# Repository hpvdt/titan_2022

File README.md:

# TITAN Video System

This is the code and hardware that is used to drive the electronics aboard TITAN for the "drive-by-video" system used for the World Human Powered Speed Challenge 2022.

>[!NOTE]
> This repository is meant to a snapshot of the system used for the 2022 system for TITAN, and was archived in November 2023. It was only unarchived to add a written summary of [operating instructions](./OPERATION.md) should it need to be reused. However no changes to the system itself have happened since 2023.
>
> For information on the the newest system in 2026 please go to that one's [separate repository](https://github.com/savob/titan_2026).

This code is spread across two types of devices, an STM32 microcontroller (STM32F103C8 is used in current models) and Raspberry Pis (RPi) Model 3B+'s. Each rider has an RPi for a total of two units, while there is only one STM32 for the vehicle. The STM32 is primarily responsible for collecting vehicle data and passing it to the RPis when requested. The RPis are responsible for displaying the video feed from the RPi Cameras used (hence why each rider needs their own) with an overlay of data collected inside the vehicle. This overlay is tailored to each rider.

There is an additional redundant video system for the front rider based on analog video to minimize potential failure points. This system was entirely off the shelf except for the power regulator, and was entirely disconnected from the remainder of TITAN's electronics to prevent any failure cascade affecting it.

## Folders

The repository is split into folders based on function.

Folder | Purpose
------ | -------
`Hardware` | Hardware files for our circuit boards
`Microcontroller Code` | STM32 Code
`vision` | RPi video code in C

## Hardware

The hardware for TITAN was all designed in [KiCad](https://www.kicad.org/) there are all three boards designed for TITAN with a `readme.md` explaining their purposes. Below is a block diagram of the TITAN system.

## Microcontroller Code

This is the collection of code prepared for the microcontroller on TITAN. It contains the unit tests we prepared when developing and testing different features that would eventually be integrated into TITAN, a local copy of the GPS library we use, and the overall program for TITAN.

TITAN was initially coded entirely within the Arduino IDE, however we migrated to using VS Code and PlatformIO to help make development easier and also make use of debugging features absent in the original Arduino IDE.

## Raspberry Pi Code

These are responsible for putting video on the displays for the riders to see, overlaid with information about TITAN. One of the RPi's has an ANT+ USB module used to collect data from the heart rate monitor and power pedals each rider has and feed it to the STM32 to pass onto the other RPi.

**The program for running the video feed is run as a separate process to the overlay**, this way if there is a hardware malfunction for the overlay (e.g. the STM32 freezes) then the video feed is uninterrupted for the riders.

The code for vision is split between Python and C. The video related code is written in Python, as well as a few other scripts for operation. The overlay code is written in C using the chipset driver library unique to the RPi 3 hardware to draw the overlay so it cannot be used on RPi models other then the 3B or 3B+ (and must be compiled specifically for each model).

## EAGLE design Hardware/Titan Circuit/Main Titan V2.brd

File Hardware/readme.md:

# TITAN Hardware

These folders contain the files related to hardware designed to operate TITAN. They were all designed using KiCad 6.0.2.

## Overview

The TITAN hardware is designed to primarily be a HAT (**HA**rdware on **T**op) for the Raspberry Pi 3B+s we use for video. This form factor was chosen to reduce the overall footprint of the system compared to the original 2019 system which used a ribbon cable between the RPi and boards. This also reduces the chance of incorrect connections since the HAT can only be seated one way. At the heart of the HAT, there is an STM32F103C microcontroller which communicates with the RPis and various sensors around TITAN via the various connections present.

These HATs perform 4 main functions:
1. Regulate power for their RPi and monitor from the battery. (Reverse polarity and undervoltage protection built in).
2. Facilitate communication between RPis via an STM32 microcontroller
3. Collect data from TITAN using the STM32 microcontroller
4. Handle telemetry with the chase vechicle

**Functions 2 to 4 are only performed on the "main" (front) unit, where the STM32 is.** The secondary (rear) does not have the STM32 mounted and just uses the power system and a header to connect to the main board for data.

## The Boards

There are three boards/folders/projects present in the folder, representing two revisions of the hardware. 

### TITAN Redux (2020)

Following feedback from the 2019 WHPSC and experience in developing [Blueshift](https://github.com/hpvdt/blueshift), an initial revision of TITAN was made in the fall of 2020, dubbed `titan_redux`. This was the main revision from the 2019 system, moving to the HAT form factor which worked on Blueshift as well as moving to embed the microconroller directly on the board (as opposed to seating a "Blue Pill" development board) and using SMT to reduce the overall size.

This was largely successful and allowed most of the code that went into TITAN in 2022 to be properly tested. There were only two notable issues with it:
1. The RX and TX lines for the GPS were not properly crossed over to the STM32.
2. The 5V regulator was removed for undocumented reasons, likely due to a failure.

### TITAN 2022

The more straightforwardly named `titan_2022` is a revision of the Redux board. It addresses the issues it had as well as adding support for new features while maintaining the same RPi HAT form. A brief of the changes:

- Fixed UART lines
- Rearranged board for improved button access
- Rearranged sensors to simplify routing
- Changed to a different 5V regulator (largely due to supply issues)
- Moved DHT sensor and encoder comparator off-board
- Added headers for monitoring CO2 and brake temperature

### TITAN Wheel (2022)

As part of the revision process from redux to the 2022 system a daughter board to collect wheel data was prepared called `titan_wheel`. This board houses the brake temperature sensor as well as the optical encoder and its conditioning circuitry. It was designed to fit within the wheel structure close to the brake disk.

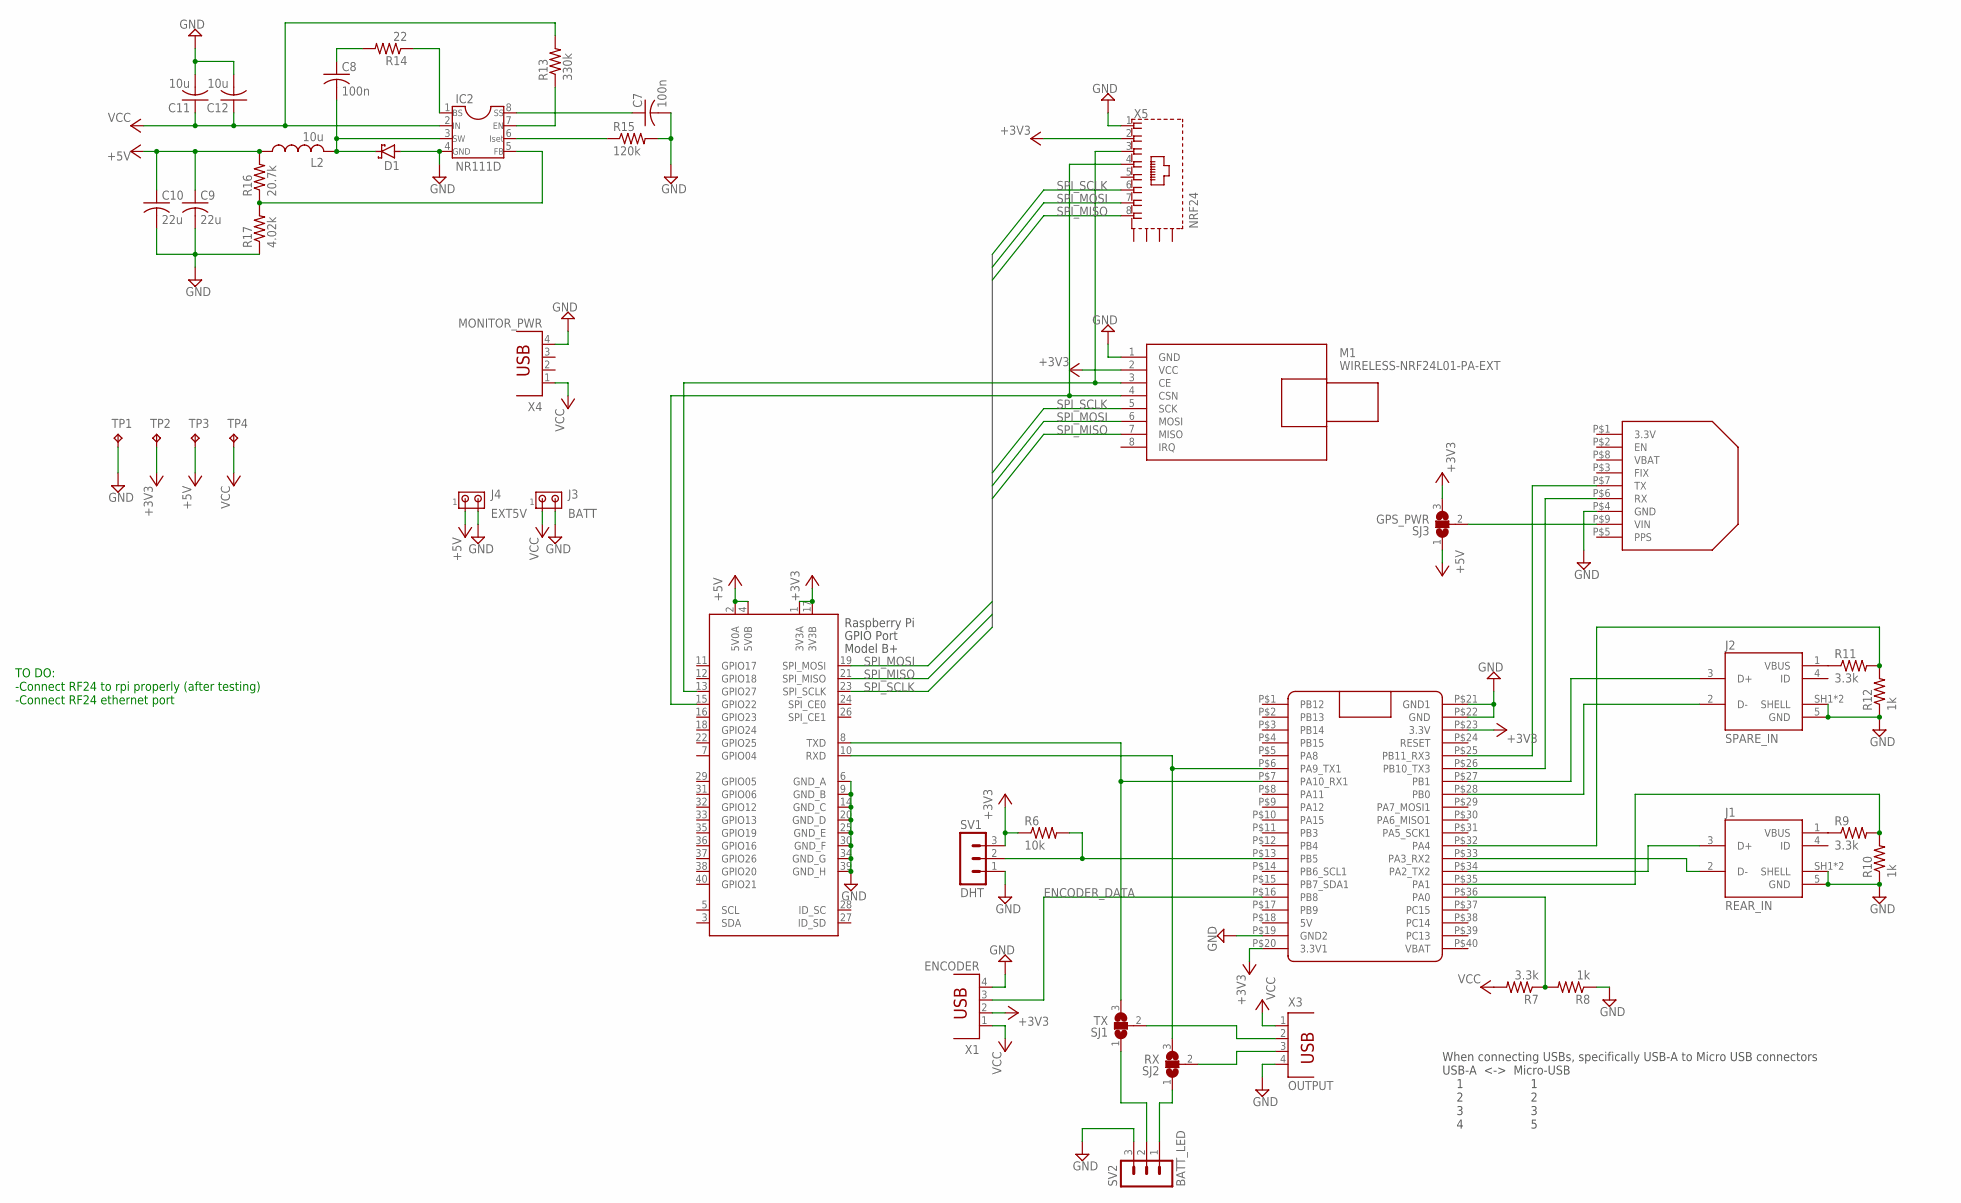
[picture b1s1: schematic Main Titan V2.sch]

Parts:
C7, C8: 100n; C050-024X044
C9, C10: 22u; C025-024X044
C11, C12: 10u; C025-024X044
D1: SCHOTTKY-DIODEC4111-15; C4111-15
IC2: NR111D; DIL08
J1: REAR_IN; TE_2172034-1
J2: SPARE_IN; TE_2172034-1
J3: BATT; 1X2MTA
J4: EXT5V; 1X2MTA
L2: 10u; INDRD650W105D880H1100B
M1: WIRELESS-NRF24L01-PA-EXT
R6: 10k; 0204/7
R7, R9, R11: 3.3k; 0204/7
R8, R10, R12: 1k; 0204/7
R13: 330k; 0204/7
R14: 22; 0204/7
R15: 120k; 0204/7
R16: 20.7k; 0204/7
R17: 4.02k; 0204/7
SJ1: TX; SJ_2
SJ2: RX; SJ_2
SJ3: GPS_PWR; SJ_2
SV1: DHT; MA03-1
SV2: BATT_LED; MA03-1
TP1: GND; TP20SQ
TP2: 3V3; TP20SQ
TP3: 5V; TP20SQ
TP4: BAT; TP20SQ
U$1: BLUE_PILL
U$3: ULTIMATE-GPS; ULTIMATE_GPS
X1: ENCODER; PN87520
X2: RPI; RASPI_GPIO_B+_BOX
X3: OUTPUT; PN87520
X4: MONITOR_PWR; PN87520
X5: NRF24; RJ45-SHIELD1

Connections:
3.3V: U$3.P$1 (3.3V)
25%LED: SJ1.1, SV2.2
50%LED: SJ2.1, SV2.1
+3V3: M1.2 (VCC), R6.1, SJ3.3, SV1.3, TP2.TP, U$1.P$20 (3.3V1), U$1.P$23 (3.3V), X1.2, X2.1 (3V3A), X2.17 (3V3B), X5.2
+5V: C9.1, C10.1, J4.1, L2.1, R16.2, SJ3.1, TP3.TP, X2.2 (5V0A), X2.4 (5V0B)
BATT_LVL: R7.1, R8.2, U$1.P$36 (PA0)
DHT: R6.2, SV1.2, U$1.P$13 (PB5)
ENCODER_DATA: U$1.P$16 (PB8), X1.3
GND: C7.2, C9.2, C10.2, C11.2, C12.2, D1.A, IC2.4 (GND), J1.5 (GND), J1.SH1 (SHELL), J1.SH2 (SHELL), J2.5 (GND), J2.SH1 (SHELL), J2.SH2 (SHELL), J3.2, J4.2, M1.1 (GND), R8.1, R10.1, R12.1, R15.2, R17.1, SV1.1, SV2.3, TP1.TP, U$1.P$19 (GND2), U$1.P$21 (GND1), U$1.P$22 (GND), U$3.P$4 (GND), X1.4, X2.6 (GND_A), X2.9 (GND_B), X2.14 (GND_C), X2.20 (GND_D), X2.25 (GND_E), X2.30 (GND_F), X2.34 (GND_G), X2.39 (GND_H), X3.4, X4.4, X5.1
GPS_RX: U$1.P$26 (PB10_TX3), U$3.P$6 (RX)
GPS_TX: U$1.P$25 (PB11_RX3), U$3.P$7 (TX)
unnamed: M1.3 (CE), X2.13 (GPIO27), X5.3
unnamed: M1.4 (CSN), X2.15 (GPIO22), X5.4
unnamed: SJ1.2, X3.2
unnamed: SJ3.2, U$3.P$9 (VIN)
unnamed: SJ2.2, X3.3
unnamed: IC2.5 (FB), R16.1, R17.2
unnamed: J1.1 (VBUS), R9.1
unnamed: J2.1 (VBUS), R11.1
unnamed: C8.2, D1.C, IC2.3 (SW), L2.2
unnamed: C8.1, R14.2
unnamed: C7.1, IC2.8 (SS)
unnamed: IC2.6 (ISET), R15.1
unnamed: IC2.7 (EN), R13.1
unnamed: IC2.1 (BS), R14.1
REARBATT: R9.2, R10.2, U$1.P$35 (PA1)
REARRX: J1.3 (D+), U$1.P$34 (PA2_TX2)
REARTX: J1.2 (D-), U$1.P$33 (PA3_RX2)
RPI_RX: SJ2.3, U$1.P$6 (PA9_TX1), X2.10 (RXD)
RPI_TX: SJ1.3, U$1.P$7 (PA10_RX1), X2.8 (TXD)
SPAREBATT: R11.2, R12.2, U$1.P$32 (PA4)
SPARELED1: J2.3 (D+), U$1.P$27 (PB1)
SPARELED2: J2.2 (D-), U$1.P$28 (PB0)
SPI_MISO: M1.7 (MISO), X2.21 (SPI_MISO), X5.8
SPI_MOSI: M1.6 (MOSI), X2.19 (SPI_MOSI), X5.7
SPI_SCLK: M1.5 (SCK), X2.23 (SPI_SCLK), X5.6
VCC: C11.1, C12.1, IC2.2 (IN), J3.1, R7.2, R13.2, TP4.TP, X1.1, X3.1, X4.1

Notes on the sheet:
When connecting USBs, specifically USB-A to Micro USB connectors USB-A <-> Micro-USB 1 1 2 2 3 3 4 5
TO DO: -Connect RF24 to rpi properly (after testing) -Connect RF24 ethernet port

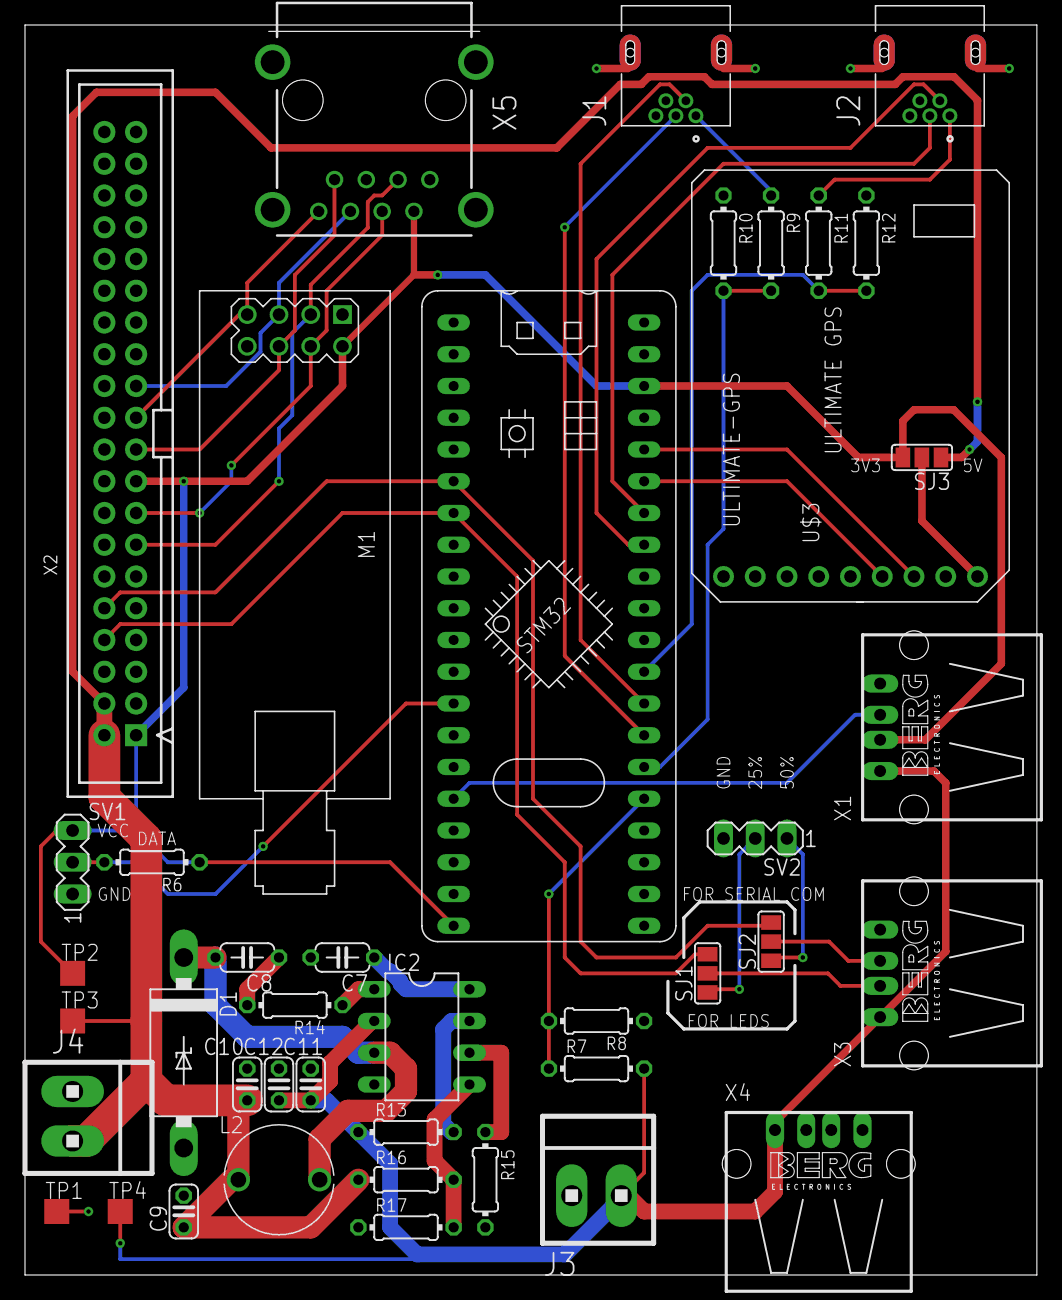
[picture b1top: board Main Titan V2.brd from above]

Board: 2 copper layers, 80.9 x 100.0 mm, 42 parts (0 on the bottom side), 36 nets.

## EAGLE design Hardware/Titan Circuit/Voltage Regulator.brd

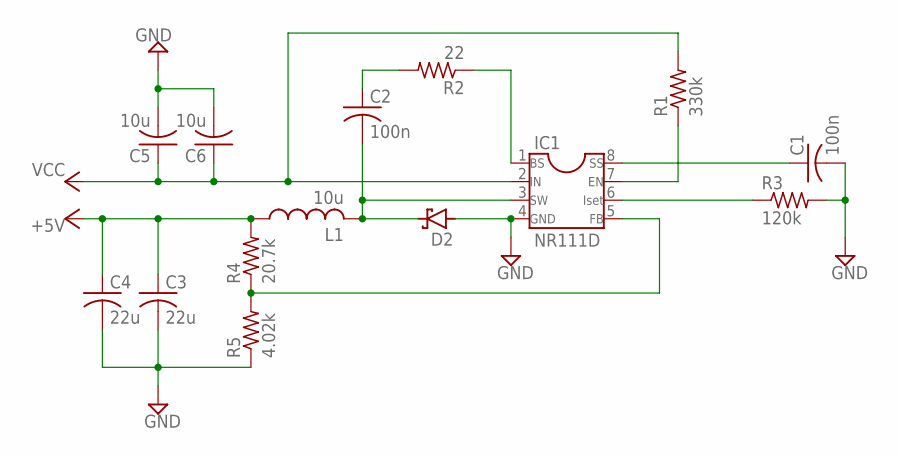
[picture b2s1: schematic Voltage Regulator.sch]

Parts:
C1, C2: 100n; C050-024X044
C3, C4: 22u; C025-024X044
C5, C6: 10u; C025-024X044
D2: SCHOTTKY-DIODEC4111-15; C4111-15
IC1: NR111D; DIL08
L1: 10u; INDRD650W105D880H1100B
R1: 330k; 0204/7
R2: 22; 0204/7
R3: 120k; 0204/7
R4: 20.7k; 0204/7
R5: 4.02k; 0204/7

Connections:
+5V: C3.1, C4.1, L1.1, R4.2
GND: C1.2, C3.2, C4.2, C5.2, C6.2, D2.A, IC1.4 (GND), R3.2, R5.1
unnamed: IC1.5 (FB), R4.1, R5.2
unnamed: IC1.1 (BS), R2.1
unnamed: IC1.7 (EN), R1.1
unnamed: C2.2, D2.C, IC1.3 (SW), L1.2
unnamed: C2.1, R2.2
unnamed: C1.1, IC1.8 (SS)
unnamed: IC1.6 (ISET), R3.1
VCC: C5.1, C6.1, IC1.2 (IN), R1.2

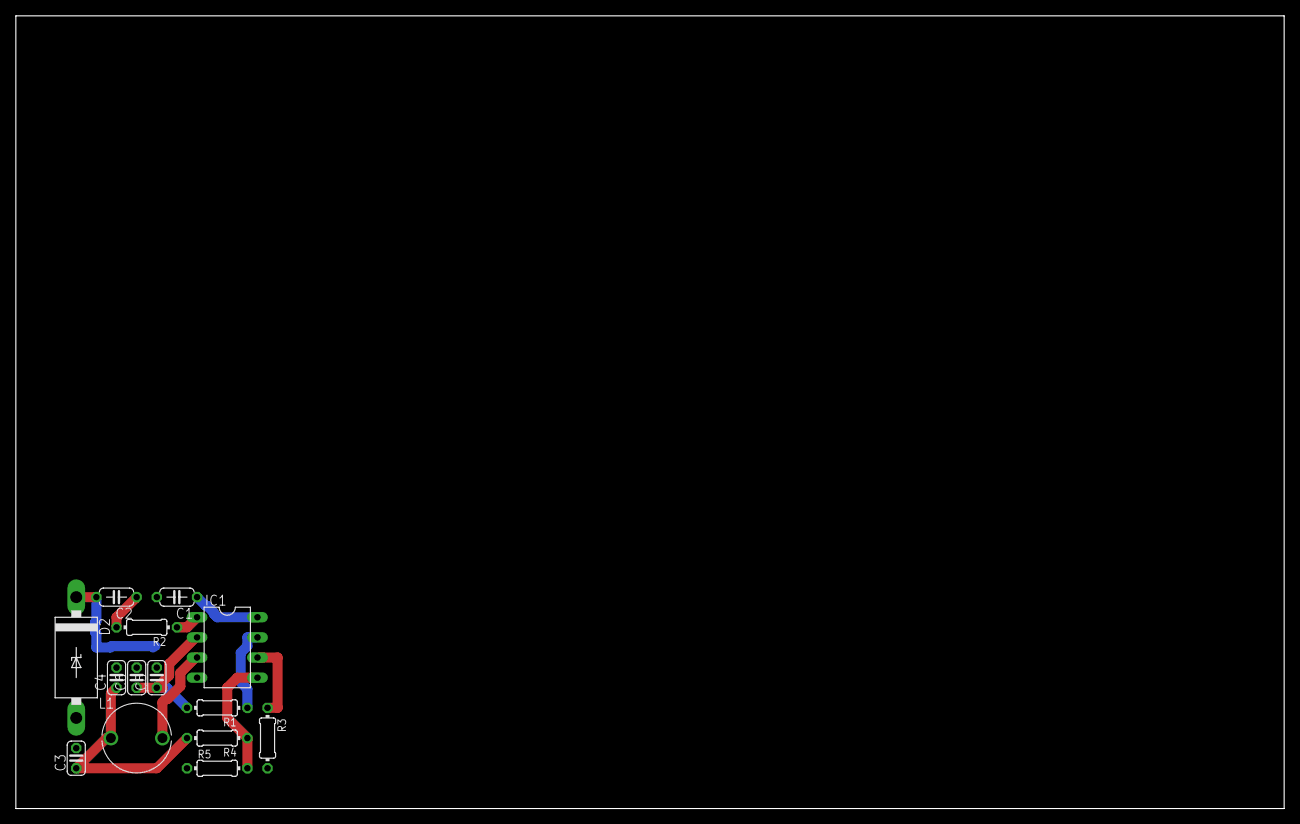
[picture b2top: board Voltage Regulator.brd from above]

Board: 2 copper layers, 160.0 x 100.0 mm, 14 parts (0 on the bottom side), 10 nets.

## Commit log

2019-11-03 Arduino code
    Initial commit
2019-11-03 Python Code
2019-11-03 Modified Python ANT+ Library
2019-11-04 Repiping errors
    - Changed OSD to use 'update' instead of layer swapping
    - Added code to output errors to a null device for the duration of 'update' to allow it to be run in terminal.
    - Cycle time cut down to ~70ms!
2019-11-07 Initiation of C++ version
    Started the C++ version folder for future use.
2019-12-24 C++ initial commit
2020-01-30 Fixing overlay
    Previous commit had a line commented out that was responsible for adding the overlay. Oops.
2020-02-07 Fixing font issues
    Made the font reference relative, not absolute to avoid issues if the folder name changes for the folder containing res and src
2021-02-20 Updated readme to be more informative
2021-06-07 Added python unit tests
2021-06-07 Added harware design files
2021-06-07 Added all microcontroller code
2021-06-07 Deleted redundant folder
2022-07-21 Delete TitanVisionFirmwarePython directory
    Not needed, moving to C-based OSD system
2022-07-21 Delete titan_vision_c++ directory
    Not using this c++ code
2022-07-21 Uploaded test files for openant
2022-07-21 Upload of C based OSD
    OSD based on writing directly to the video driver
2022-07-22 Initial working version with ANT
    Made a version that receives and shows the ANT data piped into the process (from the python ANT scripts)
2022-07-22 Delete titanant.py
    Moved to directory with other OSD code
2022-07-22 Marking out the need to update readme
2022-07-22 Added code to start and stop camera preview
2022-07-23 Updated Serial object definition
    Updated Serial object declaration to be in line with new STM32 core
    https://github.com/stm32duino/wiki/wiki/API#hardwareserial
2022-07-23 Chenged Serial object names
2022-07-23 Removed spare system code
2022-07-23 Removed LED code
2022-07-24 Made python script ignore temporary pipe issues
2022-07-24 Improved debug messaging for serial communication
2022-07-24 Matching STM32 specified baudrate
2022-07-24 Added system to disable camera for tests
2022-07-24 Moved variables into .c file forbetter scoping
2022-07-25 Migrated ANT code to seperate files
2022-07-25 Tidied up startup messages
2022-07-25 Redid check for serial line ANT
2022-07-25 Moved debug define into .c file
2022-07-25 Changed up ANT debug messages
2022-07-25 Redid timing related code
2022-07-25 Changed NULL to character constant
2022-07-25 Fixed string termination
2022-07-25 Added new time trial file for ease of use in other files
2022-07-25 Added serialTest file
2022-07-25 Added ability to batch send ANT data
2022-07-25 Setting stdin to non-blocking
2022-07-25 Added logging capabilities
2022-07-25 Added file for log directory
2022-07-25 Updated makefile to include new files
2022-07-27 Ported racesim to C
2022-07-27 Added comments for clarity
2022-08-02 Moving C log files into correct folder
2022-08-02 USB debugging to be toggled by build settings
2022-08-03 Added telemetry functionality
2022-08-03 Added Arduino based telemetry station code
2022-08-03 Added check for presence of a radio
2022-08-04 Added radio check to station code
2022-08-04 Fixed variable change
2022-08-04 Updated GPS code
2022-08-04 Removed comment for serial pins
2022-08-04 Fixed integer division for GPS distance
2022-08-04 Removed irrelevant encoder test code
2022-08-04 Added hardware timer test code
2022-08-04 Removed useless SPI related code
2022-08-15 Removing hardware files from 2019
2022-08-15 Upload of my 2020 redux hardware
2022-08-15 Uploaded TITAN 2022 electronics system as ordered
2022-08-15 Created hardware readme
2022-08-16 Cleaned up schematics
2022-08-17 Added scripts to start system and safely power down
2022-08-17 Allow program to be altered using arguements when called
2022-08-17 Accomodating new data from bike
2022-08-17 Began seperate overlays for riders
2022-08-18 Condensed arguement calls
2022-08-18 Fixing arguement parsing indexes
2022-08-18 Cleaned up ANT data handling
2022-08-18 Tuned overlay layouts for riders
2022-08-18 All log files/videos are indexed by file count in their names
2022-08-18 Updated start script to have right arguements for bike.bin
2022-08-19 Incorperating RaceSim
2022-08-19 Changed radio message variable name
2022-08-19 Added brake temperature
2022-08-19 Added CO2 sensor support
2022-08-19 Disabled radio prints
2022-08-19 Minor touches
2022-08-19 Added note for new data
2022-08-19 Moved some debug related stuff inside '#ifdef'
2022-08-19 Upload of inital PlatformIO based firmware
2022-08-19 Moved brake code to seperate files
2022-08-19 Moved telemetry, condensed main loop
2022-08-19 Added LED library
2022-08-19 Added hardware timer based encoder
2022-08-23 Fixed note for wheel LED
2022-08-23 Added build option for clone STM32s
2022-08-23 Removed redundant debug message
2022-08-23 Added checks for if a brake is missing or not
2022-08-23 Fixed heartbeat and added LED flashes in setup
2022-08-28 Fixed reading for rear brake temperature
2022-08-28 Added debug configuration
2022-08-30 Calibrated battery voltage division
2022-09-01 Added colour to C code print statements
2022-09-01 Explicitly make it run forever when numFrames is -1
2022-09-01 Matched serial lines with hardware
2022-09-01 Fixed original encoder code
2022-09-01 Tweaked battery system based on tests
2022-09-01 Make GPS distance a float division
2022-09-01 Hardcoded emissivity for brake disks
2022-09-06 Add GPS spd to display. Change power to avg power.
2022-09-07 divided circumference value by 1000
2022-09-07 modified files to work on raspberry pi
2022-09-07 Added ledSet and comments
2022-09-07 Added polling for CO2 sensor
2022-09-07 Interrupt based CO2 sensor monitoring
2022-09-07 Added blinking to brakes for error pick up
2022-09-07 Touching up some headers
2022-09-07 Added passthrough code for TITAN redux board
2022-09-12 Made one unified radio passthrough sketch
2022-09-12 Removed obsolete and outdated Arduino sketch for TITAN
2022-09-12 Fixed CO2 reading
2022-09-12 Implemented bilk data system for telemetry
2022-09-12 Added error LEDs to setups
2022-09-12 Set default radio power to maximum
2022-09-13 Changed name for encoder speed
2022-09-14 Generalized bulk transfer for RPis too
2022-09-14 Changed speed variable names for clarity and logging GPS distance
2022-09-15 Fixed power averaging issue
2022-09-15 Fixed return to desktop script
2022-09-15 Properly named ANT files
2022-09-15 Changed periodic power averaging to continuous averaging
2022-09-16 Added .gitignore
2022-10-02 Added/changed readmes
2022-12-31 Raised radio power to MAX
    Explains the short range of TITAN at WHPSC 2022. This should be tested for stability due to power draw, low if needed.
2023-01-16 Uploading block diagram file
2023-03-08 Updated readme with block diagram
2023-11-08 Update platformio.ini
    Made debugging server interpolated based on user install
2026-05-04 Added operation guide
2026-05-04 Spelling mistake

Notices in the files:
parts and their libraries:
diy-modules: Released under the Creative Commons Attribution 4.0 International License: http://creativecommons.org/licenses/by/4.0
